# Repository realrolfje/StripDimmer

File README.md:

# StripDimmer
This is a simple project to re-create an incandescant lightbulb effect with an RGB light strip. 

## Features:
- Automatically fades to 25% warm glow when you enter the room, turns off when you leave.
- Touch sensor to switch to full brightness (and off again).
- At low brightness, the LED strip will have a warmer (orange/red) color. 
- At full brightness, the LED strip will have a bright cool white color.
- Measures light; When it's dark, it will not (automatically) turn on.

## Requirements
To build this project, you need:
- An Arduino Nano v3.0
- 3x BUK555 Field Effect Transistor
- HC-SR501 PIR sensor (or compatible)
- Light Dependant Resistor (LDR)
- A 12V RGB LED strip with common anode (common +)
- A couple of resistors, LEDs, wires and an Electrolytic Capacitor, see schematic.

## How to upload this program to the Arduino
1. Copy the libraries in this project into the libraries folder of your Arduino installation.
2. Open the `StripDimmer.ino` file with the Arduino IDE.
3. Select the Nano as board, and the AVRISP as programmer (or the one you normally use)
4. Upload.

## How to build the project
Plug the Arduino Nano into a breadboard, and build the circuit according to the schematic below, also found as eagle file in the schematics folder. Find a value for the 1~10k resistor so that a dark LDR will make A0 reach at most 5 Volts. Hook up your LED strip and test the software.

Schematics are edited in [Eagle](http://www.cadsoftusa.com/eagle-pcb-design-software/schematic-editor/).

### Calibrating colors
When the colors look off, check that you didn't mix up the red, green and blue LEDs of your led strip. Depending on the manufacturer or production run of your LED strip, the colors might not look like what you expected. Or maybe you want to dim it from green to purple. You can do just that by changing the `colorcurve` arrray in `colorCurve.ino`. 

You have two tools to do this:

1. In the documentation folder, there is an excel sheet which shows the different PWM values, plotted as a graph. In this graph you can see that in my software, I never give more than 50% energy to the blue LEDs, because these make the color too cold/blue. You can play with the values in the sheet and try to find a smooth "curve", and put that in the software. This requires a bit of guesswork, so it's better to use rool number 2:
2. In `testStuff.ino`, there is a function called `colorMixer()`. Call this method in the `loop()`. After the Arduino starts up, open the Serial Monitor of the Arduino IDE. You can now play with the RGB values as follows:
    - For more red, press `Shift-R`, for less red, press `r`.
    - For more green, press `Shift-G`, for less red, press `g`.
    - For more blue, press `Shift-B`, for less red, press `b`.
    
In the serial monitor, the software will print the current PWM values. Use this to judge the color and build your color curve.

### Calibrating the touch sensor
The touch sensor uses the [Capsense](http://playground.arduino.cc/Main/CapacitiveSensor?from=Main.CapSense) library, which pulses one pin and measures how long it takes for the other pin to follow. When you touch the sense pin, you become a capacitance to ground, which turns the resistor into a lowpass filter, which in turn makes the sense pin slower in following the output pin.

For the touch sensor to work reliably you need to connect the negative of the Arduino to earth. Ideally this would be the ground pin of the wall socket. If that is not available, connect it to the copper water pipe or heating pipes in your house. Not grounding your circuit will make the sensing very unreliable.

When the touch sensor does not react, decrease the `touchSensitivity` value in `StripDimmer.ino`. When the touch sensor randomly reacts, increase the value.

Uncomment the `#define DEBUG` line to enable debug logging. The StripDimmer will report what it is doing, and what the touch values are when you touch the sensor. The yellow led will also light up when a touch is detected.

### Calibrating the Light sensor
The Light Depending Resistor will not be accurate, and the light in your house is probably different from mine. Of course, when the LED strip is on, the LDR will see this, so we need to compensate for that. In my case, the resistance of the LDR is lower when light shines on it. This means that in the configuration in the schematic, a lower value at `A0` means more light.

There are two settings for the LDR sensitivity:

- `darkness`: The value at A0 at which the Arduino will consider the house to be "dark".
- `darknessWithDimmedLights`: When the LED strip is at 25%, this value will be used to consider the house to be "dark", apart from the lights from the LED.

The first thing to calibrate it the `darkness` value. Uncomment the `#define DEBUG` line in `StripDimmer.ino`. This will turn on logging, and also will reduce the reaction times so you can test quicker. Turn off the lights and make it dark in your house. Check the log output, and try to trigger the PIR sensor. Increase the value for `darkness` if the PIR sensor does not react.

Turn on the lights in the house (not the LED strip). Make sure you can not trigger the PIR sensor now. If you can still trigger it, decrease the value for `darkness`.

Now do the same checks, but for the situation where the LED strip is 25% dimmed. When it is dark in the house, and the LED strip turns on because you moved, make sure you can still trigger the LDR while the LED strip is 25% on. Adjust the `darknessWithDimmedLights` value the same way as you did `darkness`.

### Calibrating the PIR sensor
The PIR sensor has two mechanical potentiometers to set sensitivity and pulse time. Set the pulse time as short as possible so we can determine that in software. Set the sensitivity of the PIR sensor so that it just reliably detects you walking into the room, not higher. You don't want a cat, a fly, or a warm gust of air from the central heating to turn on the lights.

### Calibrating the LED on/off timing
Although the settings should be correct, you may want to make the StripDimmer slower or faster in turning off the lights when you leave. To do this you can change the following values, below the `define LOGLEVEL LOG_LEVEL_INFO` line:

- `keepBrightMs`: When the StripDimmer is at full brightness (the user touched the sensor), this is the time it takes before the lights are (very slowly) dimmed back to 25%. The default is 5 minutes. PIR activity resets the timer and turns the brightness back to 100% if it started dimming.
- `keepOnDimMs`: When the StripDimmer turned the lights from 100% to 25% because of lack of PIR activity, this is the time before it switches to 0%. The default is 2 hours. PIR activity within this time resets the timer and turns the lights back on. This is designed so that you can walk out of the kitchen, and when you walk back into the kitchen to resume kooking, the StripDimmer will go back to 100% brightness.
- `keepOffDimMs`: When the StripDimmer is at 25%, this is the time after which de StripDimmer decides to switch the lights off. The default is 1 minute. PIR activity within this time resets the timer and keeps the lights at 25%.

### Putting it in a housing
Be creative. A metal housing is best, both for radiated electromagnetic noise from the PWM, but also for being resistant to external noise which can interfere with the touch or PIR sensor. Tips to think about before picking up a drill:
- Pay attention to the cooling fins of the BUK555. They are connected to the DRAIN, so you should isolate them from ground. Check the [BUK555 datasheet](documentation/BUK555-100A%20N%20Channel%20PowerMOS%20TTL%20FET.pdf?raw=true).
- Make sure you place the PIR sensor in a smart place. The corned or a room is best, check the [datasheet of the PIR sensor](documentation/HC-SR501-PIR%20Sensor.pdf?raw=true) to see the viewing angle of the sensor.
- Polish an aluminum strip to double as a touch sensor and reflector to hide the LED strip.

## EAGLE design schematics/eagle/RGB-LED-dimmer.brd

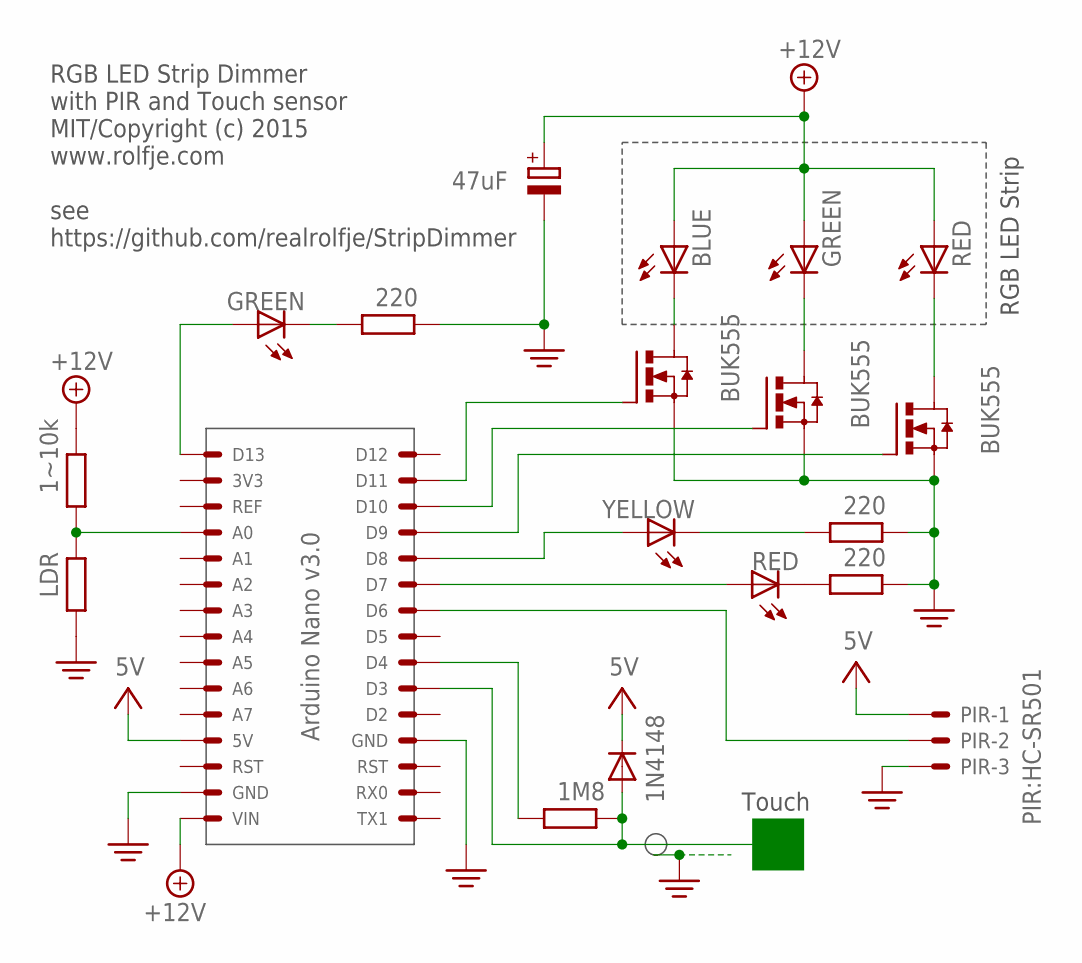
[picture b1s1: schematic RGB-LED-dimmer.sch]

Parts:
A: C-GRID-15-70543; 70543-15
B: C-GRID-15-70543; 70543-15
BLUE: LED5MM
C1: 47uF; E2,5-5
D1: 1N4148; DO35-7
GREEN: LED5MM
LDR: LDR; 0204/7
LED1: YELLOW; LED5MM
LED2: RED; LED5MM
LED3: GREEN; LED5MM
PIR: PIR:HC-SR501; 70543-03
Q1, Q2, Q3: BUK555; TO262-V
R1: 1M8; 0204/7
R2, R3, R4: 220; 0204/7
R5: 1~10k; 0204/7
RED: LED5MM

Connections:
+12V: A.15, BLUE.A, C1.+, GREEN.A, R5.2, RED.A
unnamed: Q1.2 (D), RED.K (C)
unnamed: GREEN.K (C), Q2.2 (D)
unnamed: BLUE.K (C), Q3.2 (D)
unnamed: B.9, R1.1
unnamed: B.4, Q1.1 (G)
unnamed: B.3, Q2.1 (G)
unnamed: B.2, Q3.1 (G)
unnamed: B.10, D1.A, R1.2
unnamed: LED1.K (C), R2.1
unnamed: LED3.K (C), R4.1
unnamed: B.5, LED1.A
unnamed: B.6, LED2.A
unnamed: LED2.K (C), R3.1
unnamed: B.7, PIR.2
unnamed: A.1, LED3.A
unnamed: A.4, LDR.2, R5.1
PE: A.14, B.12, C1.-, LDR.1, PIR.3, Q1.3 (S), Q2.3 (S), Q3.3 (S), R2.2, R3.2, R4.2
V+: A.12, D1.C, PIR.1

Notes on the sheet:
Arduino Nano v3.0
D11
D12
D10
GND
RX0
TX1
RST
D13
3V3
REF
VIN
Touch
RGB LED Strip
RGB LED Strip Dimmer with PIR and Touch sensor MIT/Copyright (c) 2015 www.rolfje.com see https://github.com/realrolfje/StripDimmer

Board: 2 copper layers, 20 parts (0 on the bottom side), 19 nets, no tracks yet.

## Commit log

2015-06-18 Initial version of strip dimmer with just PWM and some commented out Serial control
2015-06-19 Faster interrupt (but slower refresh) - does not work nicely
2015-06-19 Working version 0 to 25% to 100% dim and back
2015-06-19 Capacitive Touch sensor working
2015-06-19 Touch Sensor working, test code moved to seperate file
2015-06-19 Added LED to touch routine for feedback. Moved test code to separate file
2015-06-19 Test Infrared detection, switches to dimmed mode. Works.
2015-06-20 Slowly dimming and color curve calculations working.
2015-06-20 PIR, Touch and dim functionality combined. Timing and functionality not complete
2015-06-20 Code cleanup, full working solution, but timing is still short.
2015-06-21 Color graph added
2015-06-30 First working version, installed in the kitchen. Touch sensor only works when touching the kitchen sink at the same time.
2015-07-04 Working version, with changed resistors and touch timing, and added LDR check when powering off in daylight so that it does not stop at 25% dim.
2015-07-04 no message
2015-07-04 Workaround for float rounding problem where dimmed light at 250 was sometimes more blue (blue ends up at 1 or 2, depending from which side you dim). Tweaked end color.
2015-07-05 Added Logging library
2015-07-05 Fixed gotoDim end condition loop.
2015-07-08 Fixed timer overflow bug.
2015-07-10 Attempt to fix a bug where the led strip does not want to exit dimmed mode after timing out in ON mode.
2015-07-12 Added logging of sensors at end of each LED strip change. Changed values for darkness so that auto-dimming begins earlier in the evening.
2015-07-12 FIne tuned behavior when turning off the lights to complete dark, and the "off" loop turns the lights on again because it was too dark.
2015-10-10 Added libraries which are required by the project
2015-10-10 Better names for directories and files
2015-10-10 Fixed the colors in the excel graph. Added descriptions for building and calibrating.
2015-10-10 Layout fixes.
2015-10-10 Layout changes
2015-10-10 Added datasheets and fixed some more layout.
2015-10-11 More markdown layout fixes.
2015-10-11 Link schematic in documentation
2015-10-11 Update LICENSE
2015-10-11 Added Eagle CAD schematics and a PNG monochrome 300dpi export for non-eagle users.
2015-10-11 Added reference to the new schematics.
2023-08-19 Schematic migrated to KiCad Replaced LEDs with NeoPixel
